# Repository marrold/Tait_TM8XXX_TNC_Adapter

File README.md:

# Tait_TM8XXX_TNC_Adapter

An adapter for the Tait TM8XXX series of radios to breakout the required GPIOs and audio tap points onto a NinoTNC compatible DB9.

Also useful for TS8107 models where the accessory port has been filled with epoxy - note that it's plausible that some TS8107s might have other essential hardware missing or the aux connectors disabled in firmware. YMMV.

## Pinout

Pinout is looking into the connector.

| Pin | Usage | Direction |
|--|--|--|
| 1 | Tx Audio | Input |
| 2 | Busy (GPIO X)     | Output | 
| 3 | PTT | Input |
| 4 | NC | N/A|
| 5 | Rx Audio | Output |
| 6 | Ground | N/A | 
| 7 | NC | N/A|
| 8 | RSSI (Optional)| Output | 
| 9 | GPIO (Optional) | In/Output| 

## Required Tools

 - T20 Torx Screwdriver
 - PZ1 Pozi Screwdriver
 - Soldering Iron
 - Solder
 - Other soldering tools

## Required Parts

 - PCB
 - 18p Micro-MaTch PCB Connector (SMD)
 - 18p Micro-MaTch Ribbon Cable (`75-100mm)
 - [Male "Ultra Thin" DB9](https://www.aliexpress.com/item/32888489053.html)
 - 4x [M3x10mm self tapping screws](https://www.orbitalfasteners.co.uk/products/m3-x-10-pan-pozi-no-1-taptite-alternative-screws-steel-bright-zinc-plated-din-7500-ce-z) 
 -  2x 4-40 Jack Screws 

## Assembling the PCB

What goes where on the board is fairly obvious.

To make sure the red Micro-MaTch connector is soldered in the correct orientation you can fit the ribbon cable to the connector before soldering and ensure the keying pin lines up with the hole in the PCB. With the DB9 facing away from you the ribbon should go to the right.

The DB9 is quite a tight fit and the edge of the board might even require a light filing depending on the tolerances of the connector and the PCB. So far I've managed to avoid this. 

## Fitting the PCB

Remove the plastic cover from the radio by levering it off the mounting points. This should reveal 4x T20 Torx bolts. Undo them and remove the lid from the radio.  

Remove the rubber bung out of the DB9 cut out if fitted, and insert the DB9 connector onto the PCB. Line it up with the mounting posts and screw in the 4x M3x10mm self tapping screws.  These will be a little stiff as they tap the required threads.

Fit the two Jack Screws into the DB9 connector.  

Connect the ribbon cable to the red connector on the radio's main board.

Replace the lid, folding and dressing the cable so it sits correctly.

## License

This project is licensed under the MIT license

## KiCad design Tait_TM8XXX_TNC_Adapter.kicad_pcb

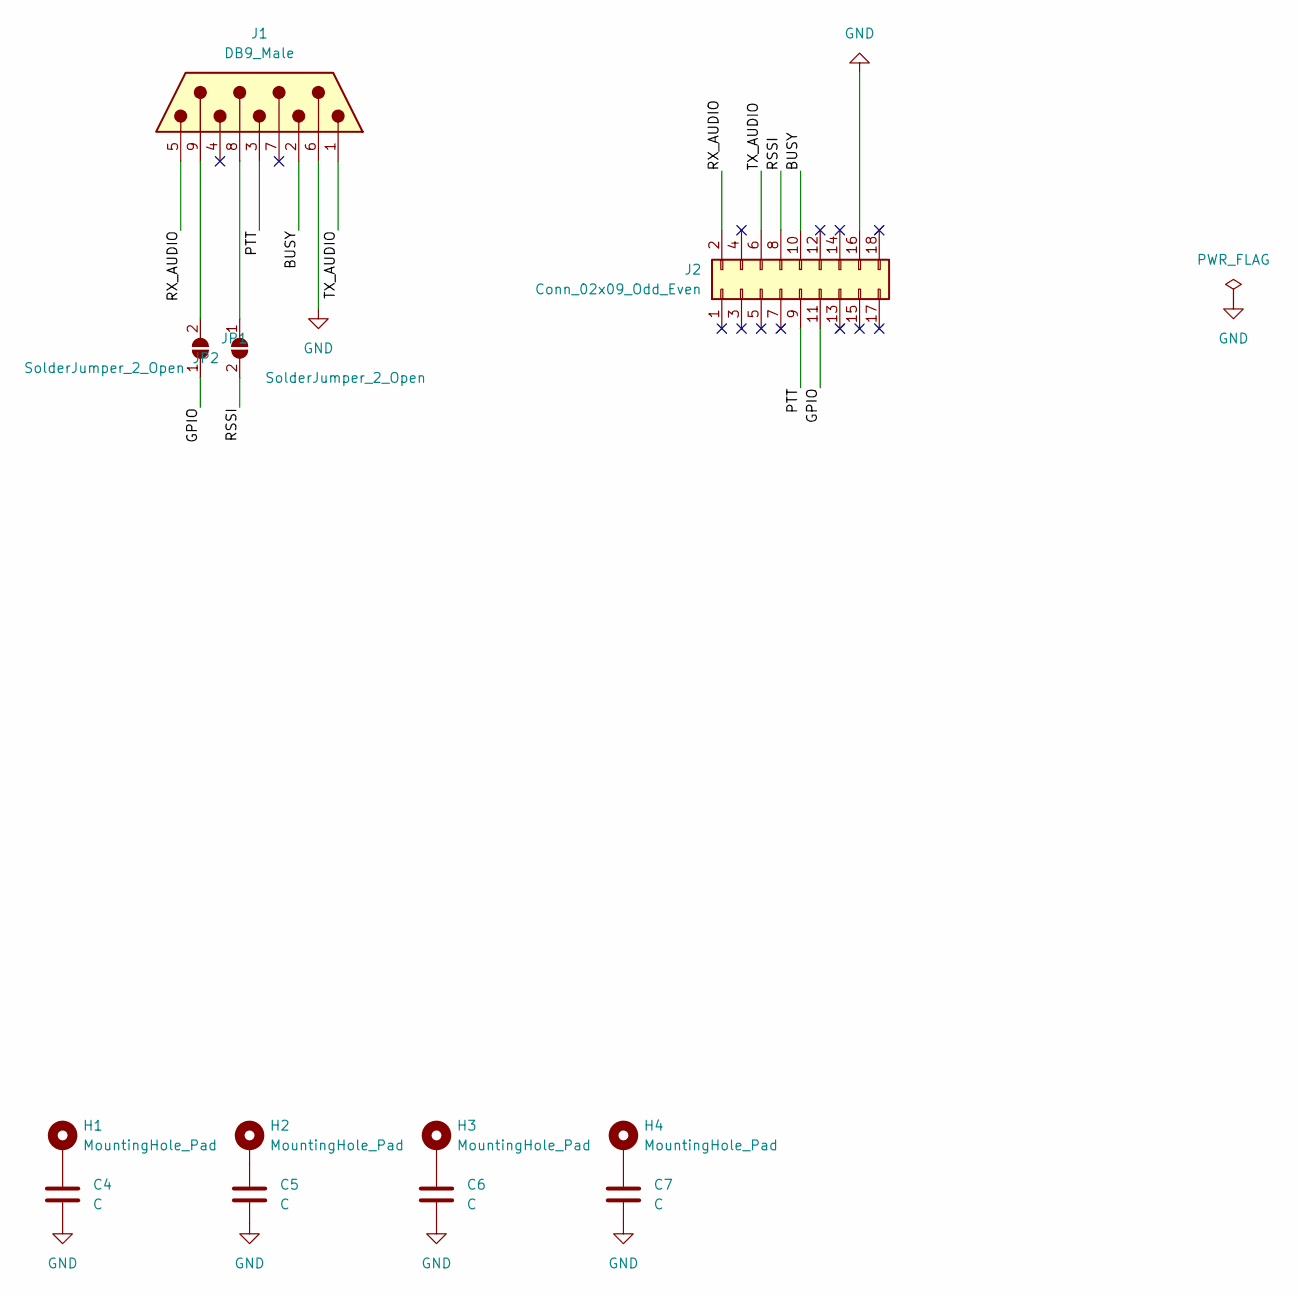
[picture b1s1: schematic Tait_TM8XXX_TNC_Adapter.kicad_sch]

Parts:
C4, C5, C6, C7: C; C_0805_2012Metric_Pad1.18x1.45mm_HandSolder
H1, H2, H3, H4: MountingHole_Pad; MountingHole_3.2mm_M3_Pad
J1: DB9_Male; DB9_Ultra-Thin_Male
J2: Conn_02x09_Odd_Even; MicroMatch-18p-SMD
JP1, JP2: SolderJumper_2_Open; SolderJumper-2_P1.3mm_Open_RoundedPad1.0x1.5mm

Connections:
/BUSY: J1.2, J2.10
/GPIO: J2.11, JP1.1 (A)
/PTT: J1.3, J2.9
/RSSI: J2.8, JP2.2 (B)
/RX_AUDIO: J1.5, J2.2
/TX_AUDIO: J1.1, J2.6
GND: C4.2, C5.2, C6.2, C7.2, J1.6, J2.16
unnamed: C4.1, H1.1
unnamed: C5.1, H2.1
unnamed: C6.1, H3.1
unnamed: C7.1, H4.1
unnamed: J1.8, JP2.1 (A)
unnamed: J1.9, JP1.2 (B)

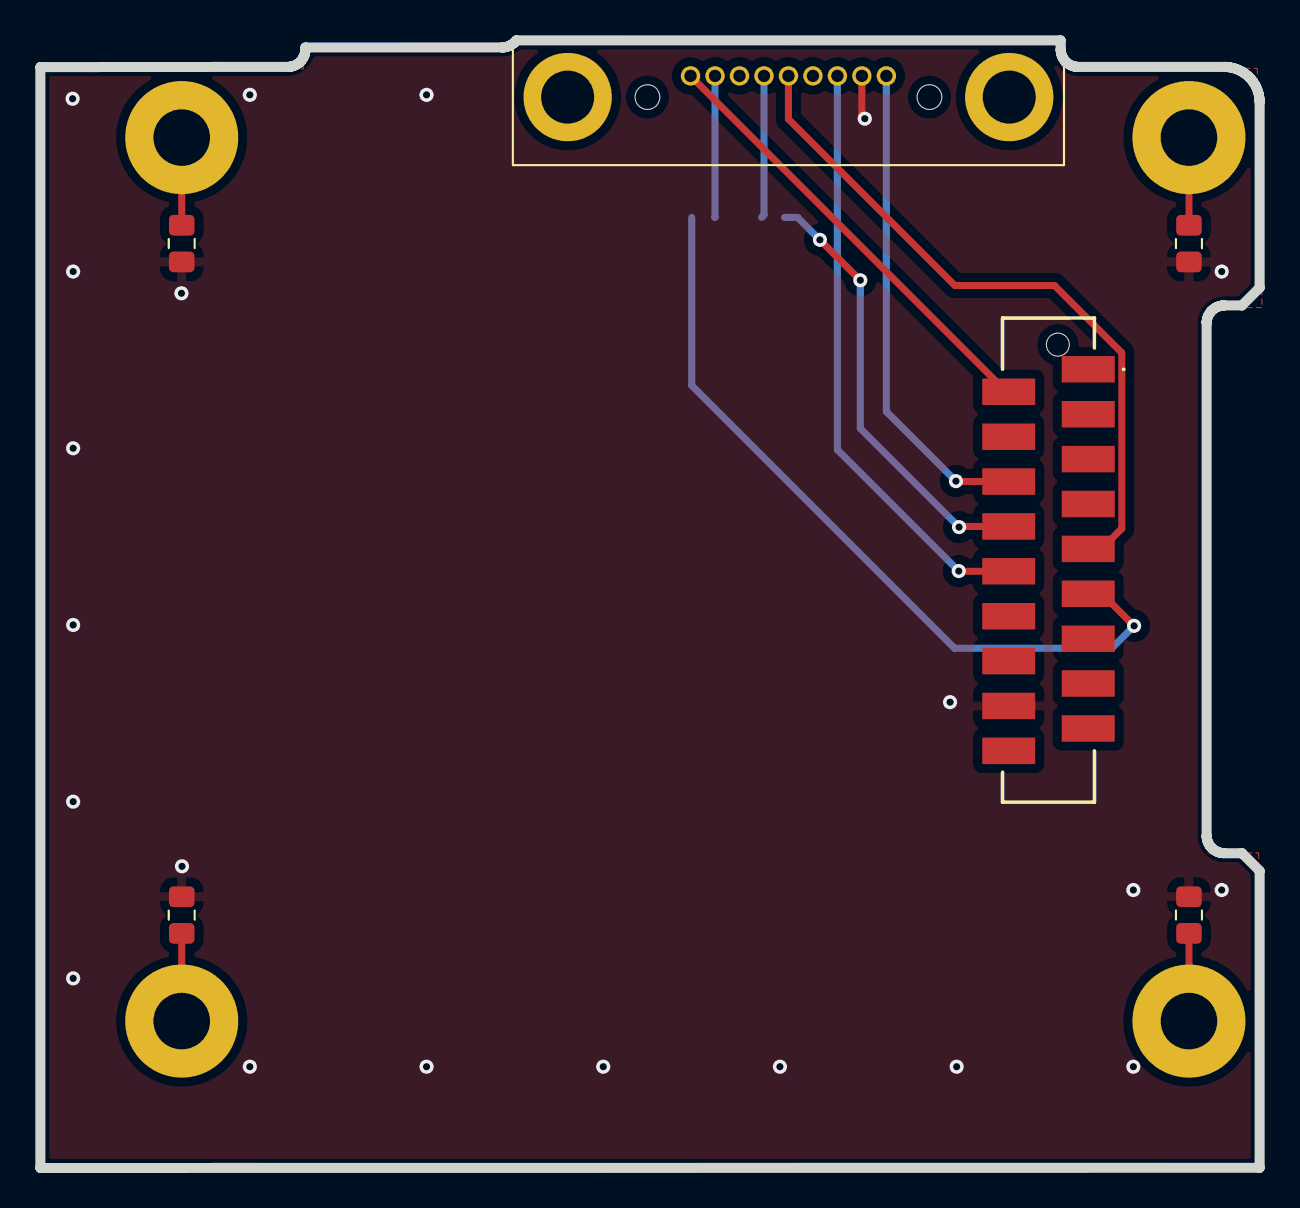
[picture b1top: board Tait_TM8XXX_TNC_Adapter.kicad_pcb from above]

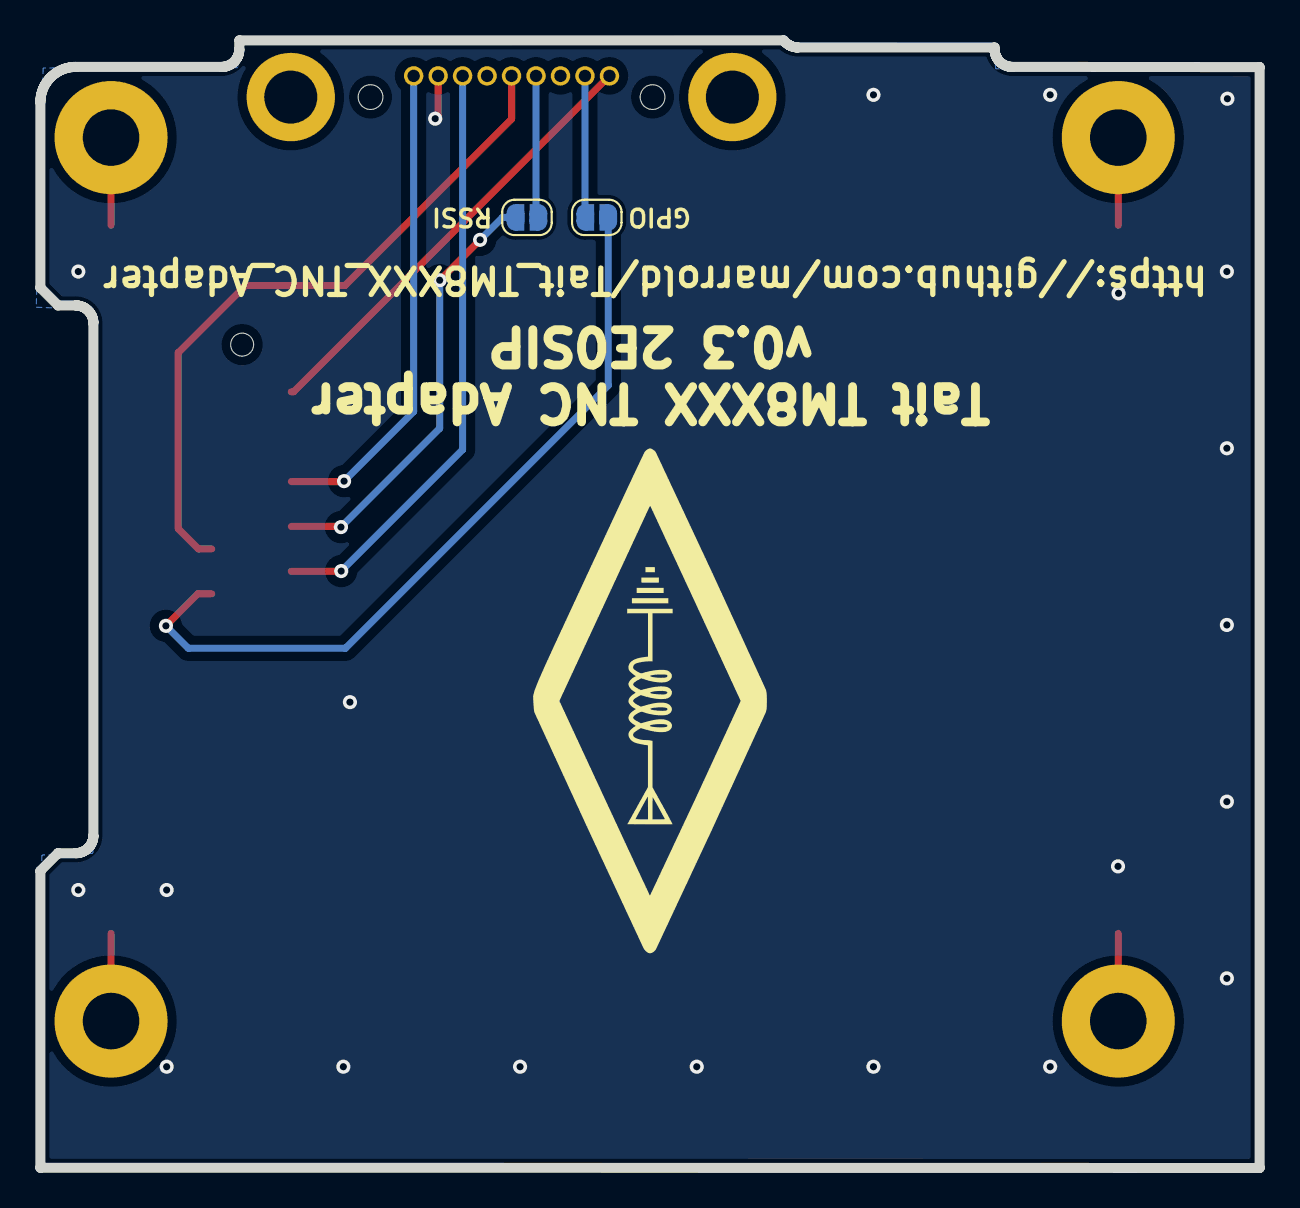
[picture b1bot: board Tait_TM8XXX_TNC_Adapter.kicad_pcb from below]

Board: 2 copper layers, 69.0 x 63.8 mm, 12 parts (2 on the bottom side), 13 nets.

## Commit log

2024-01-03 init
2024-01-03 Add Gerbers
2024-01-30 Update README.md
    Update incorrect parts
